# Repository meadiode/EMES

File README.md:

# EMES - Epic Minimalist Entertainment System

**EMES** - is a very minimalistic DIY handheld game console. 

Work in progress.

EMES has the following specifications:

 - Screen: 15x10 pixels, LED
 - Input: four button keyboard
 - Sound: Magnetic buzzer
 - Physical dimensions(approx): 40x32x14mm 
 - Removeable 8-pin cartridges

The console doesn't have an onboard CPU/MCU, instead an MCU is placed on every removable cartridge.

Each cartridge features an ATTiny10 MCU with the following specs:

 - Speed 8MHz
 - Peogram/data flash: 1KB
 - RAM: 32 bytes
 - IO: 4
 - ADC: 8bit

## Games

 - Pong
 - Snek - a snake variant, edge wrapping
 - Egg -  a N1ntend0 Game & Watch-like egg-catching game 
 - Brik - a Tetris-like
 - Simon - Simon Says

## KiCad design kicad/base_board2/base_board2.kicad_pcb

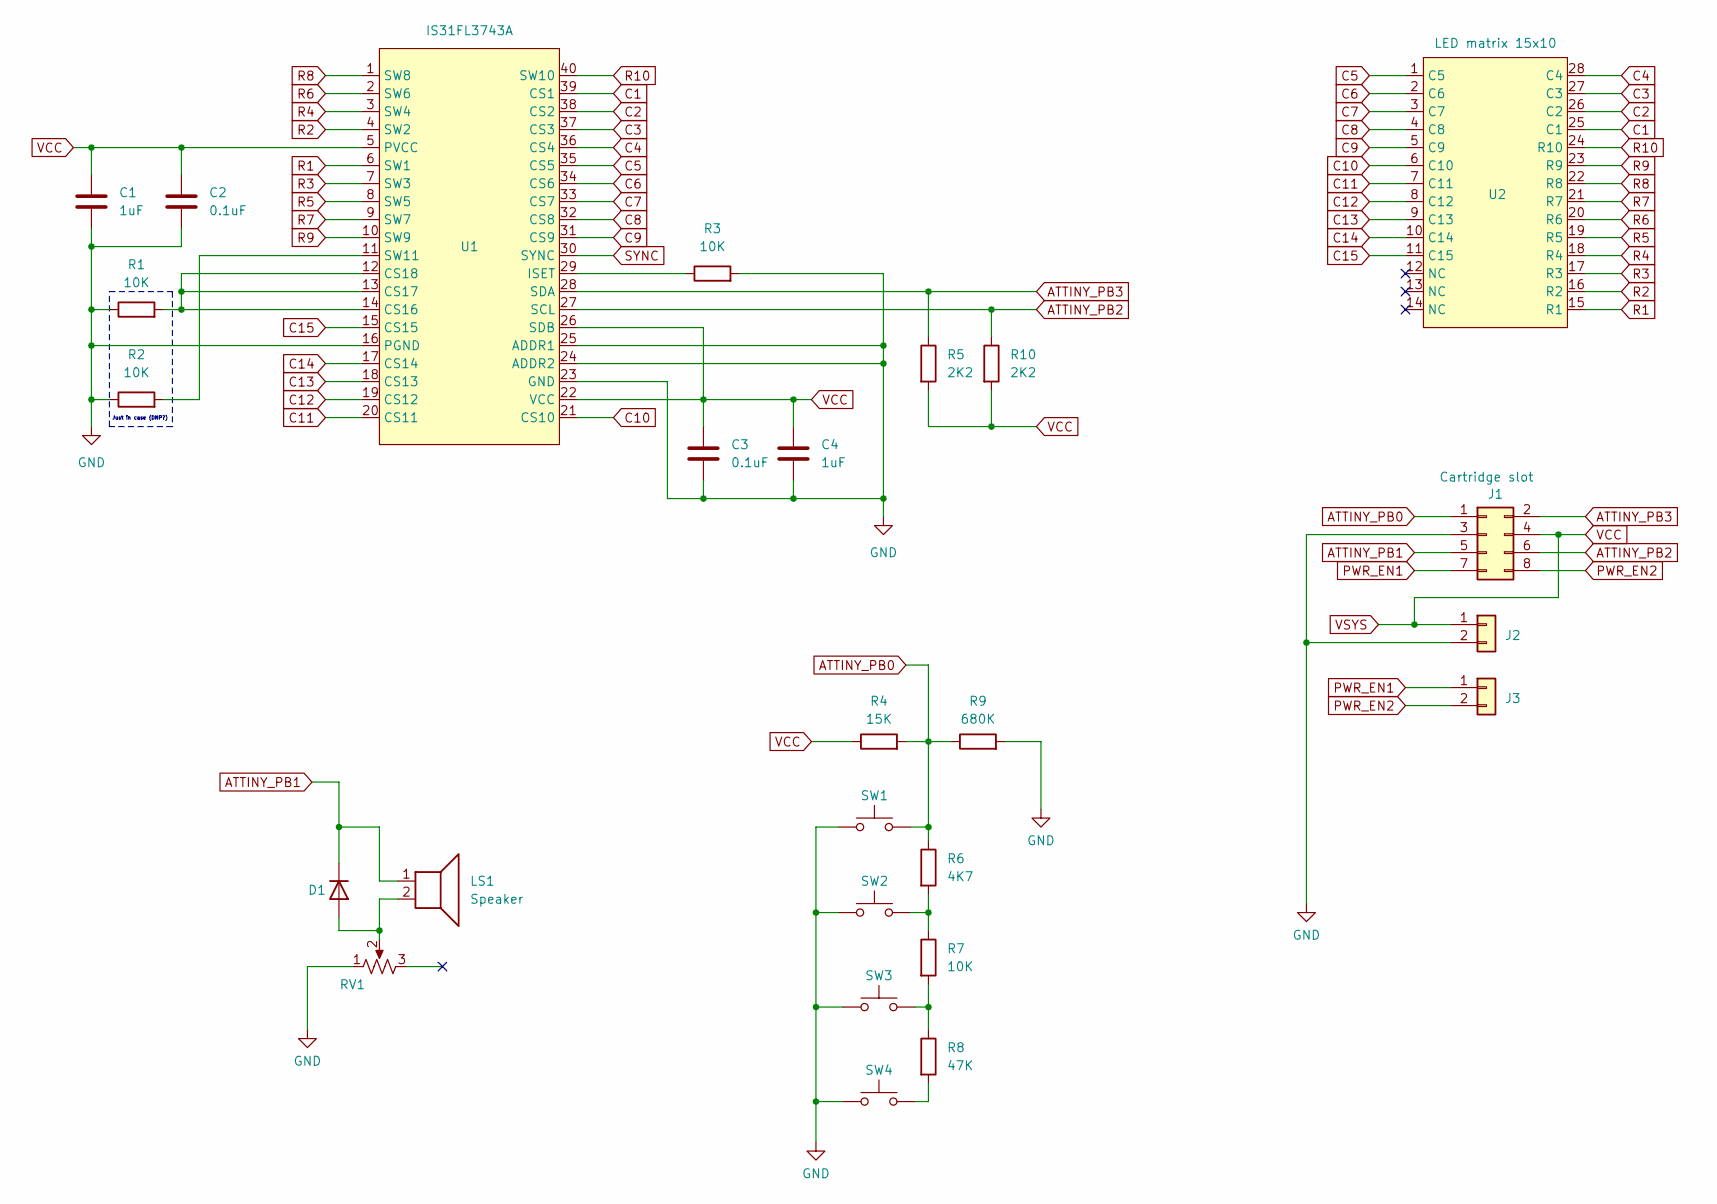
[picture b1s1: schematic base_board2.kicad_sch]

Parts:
C1, C4: 1uF; C_0603_1608Metric
C2, C3: 0.1uF; C_0603_1608Metric
D1: D; D_SOD-123
J1: Conn_02x04_Odd_Even; card_edge_2x4
J2, J3: Conn_01x02; Pads_1x2mm_2x
LS1: Speaker; Speaker_28908A
R1, R2, R3, R7: 10K; R_0603_1608Metric
R4: 15K; R_0603_1608Metric
R5, R10: 2K2; R_0603_1608Metric
R6: 4K7; R_0603_1608Metric
R8: 47K; R_0603_1608Metric
R9: 680K; R_0603_1608Metric
RV1: R_Potentiometer_US; ST-4EA
SW1, SW2, SW3, SW4: SW_Push; TS18_TACTILE_SWITCH
U1: IS31FL3743A; UQFN-40
U2: LED matrix 15x10; led_matrix_pcb_pads

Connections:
ATTINY_PB0: J1.1, R4.2, R6.1, R9.1, SW1.2
ATTINY_PB1: D1.1 (K), J1.5, LS1.1
ATTINY_PB2: J1.6, R10.1, U1.27 (SCL)
ATTINY_PB3: J1.2, R5.1, U1.28 (SDA)
C1: U1.39 (CS1), U2.25 (C1)
C2: U1.38 (CS2), U2.26 (C2)
C3: U1.37 (CS3), U2.27 (C3)
C4: U1.36 (CS4), U2.28 (C4)
C5: U1.35 (CS5), U2.1 (C5)
C6: U1.34 (CS6), U2.2 (C6)
C7: U1.33 (CS7), U2.3 (C7)
C8: U1.32 (CS8), U2.4 (C8)
C9: U1.31 (CS9), U2.5 (C9)
C10: U1.21 (CS10), U2.6 (C10)
C11: U1.20 (CS11), U2.7 (C11)
C12: U1.19 (CS12), U2.8 (C12)
C13: U1.18 (CS13), U2.9 (C13)
C14: U1.17 (CS14), U2.10 (C14)
C15: U1.15 (CS15), U2.11 (C15)
GND: C1.2, C2.2, C3.2, C4.2, J1.3, J2.2, R1.1, R2.1, R3.2, R9.2, RV1.1, SW1.1, SW2.1, SW3.1, SW4.1, U1.16 (PGND), U1.23 (GND), U1.24 (ADDR2), U1.25 (ADDR1)
unnamed: D1.2 (A), LS1.2, RV1.2
unnamed: R6.2, R7.1, SW2.2
unnamed: R7.2, R8.1, SW3.2
unnamed: R8.2, SW4.2
unnamed: R1.2, U1.12 (CS18), U1.13 (CS17), U1.14 (CS16)
unnamed: R3.1, U1.29 (ISET)
unnamed: R2.2, U1.11 (SW11)
PWR_EN1: J1.7, J3.1
PWR_EN2: J1.8, J3.2
R1: U1.6 (SW1), U2.15 (R1)
R2: U1.4 (SW2), U2.16 (R2)
R3: U1.7 (SW3), U2.17 (R3)
R4: U1.3 (SW4), U2.18 (R4)
R5: U1.8 (SW5), U2.19 (R5)
R6: U1.2 (SW6), U2.20 (R6)
R7: U1.9 (SW7), U2.21 (R7)
R8: U1.1 (SW8), U2.22 (R8)
R9: U1.10 (SW9), U2.23 (R9)
R10: U1.40 (SW10), U2.24 (R10)
SYNC: U1.30 (SYNC)
VCC: C1.1, C2.1, C3.1, C4.1, J1.4, J2.1, R4.1, R5.2, R10.2, U1.5 (PVCC), U1.22 (VCC), U1.26 (SDB)

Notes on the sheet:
Just in case (DNP?)

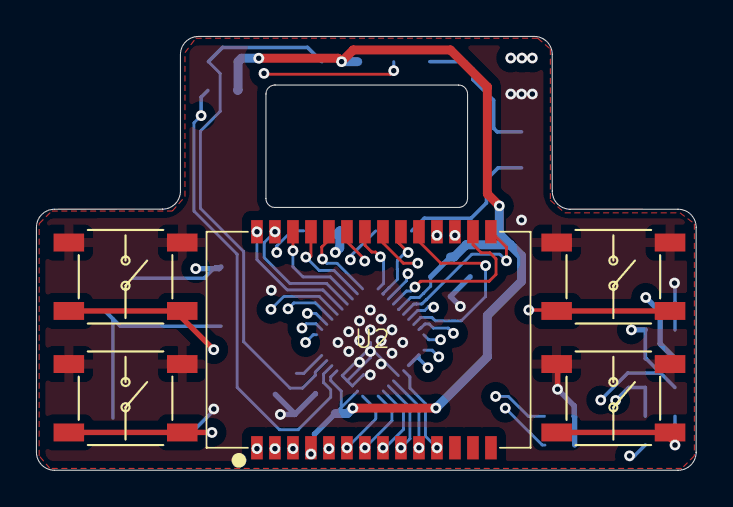
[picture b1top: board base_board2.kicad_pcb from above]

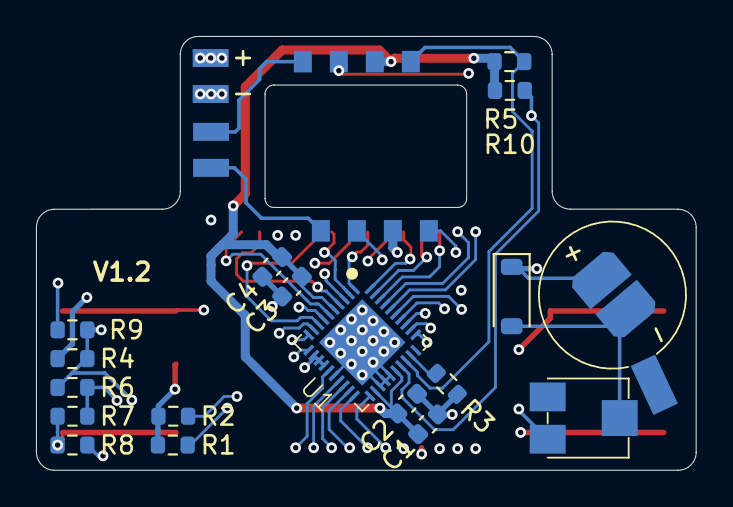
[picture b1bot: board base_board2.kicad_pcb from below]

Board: 4 copper layers, 36.7 x 24.1 mm, 26 parts (21 on the bottom side), 40 nets.

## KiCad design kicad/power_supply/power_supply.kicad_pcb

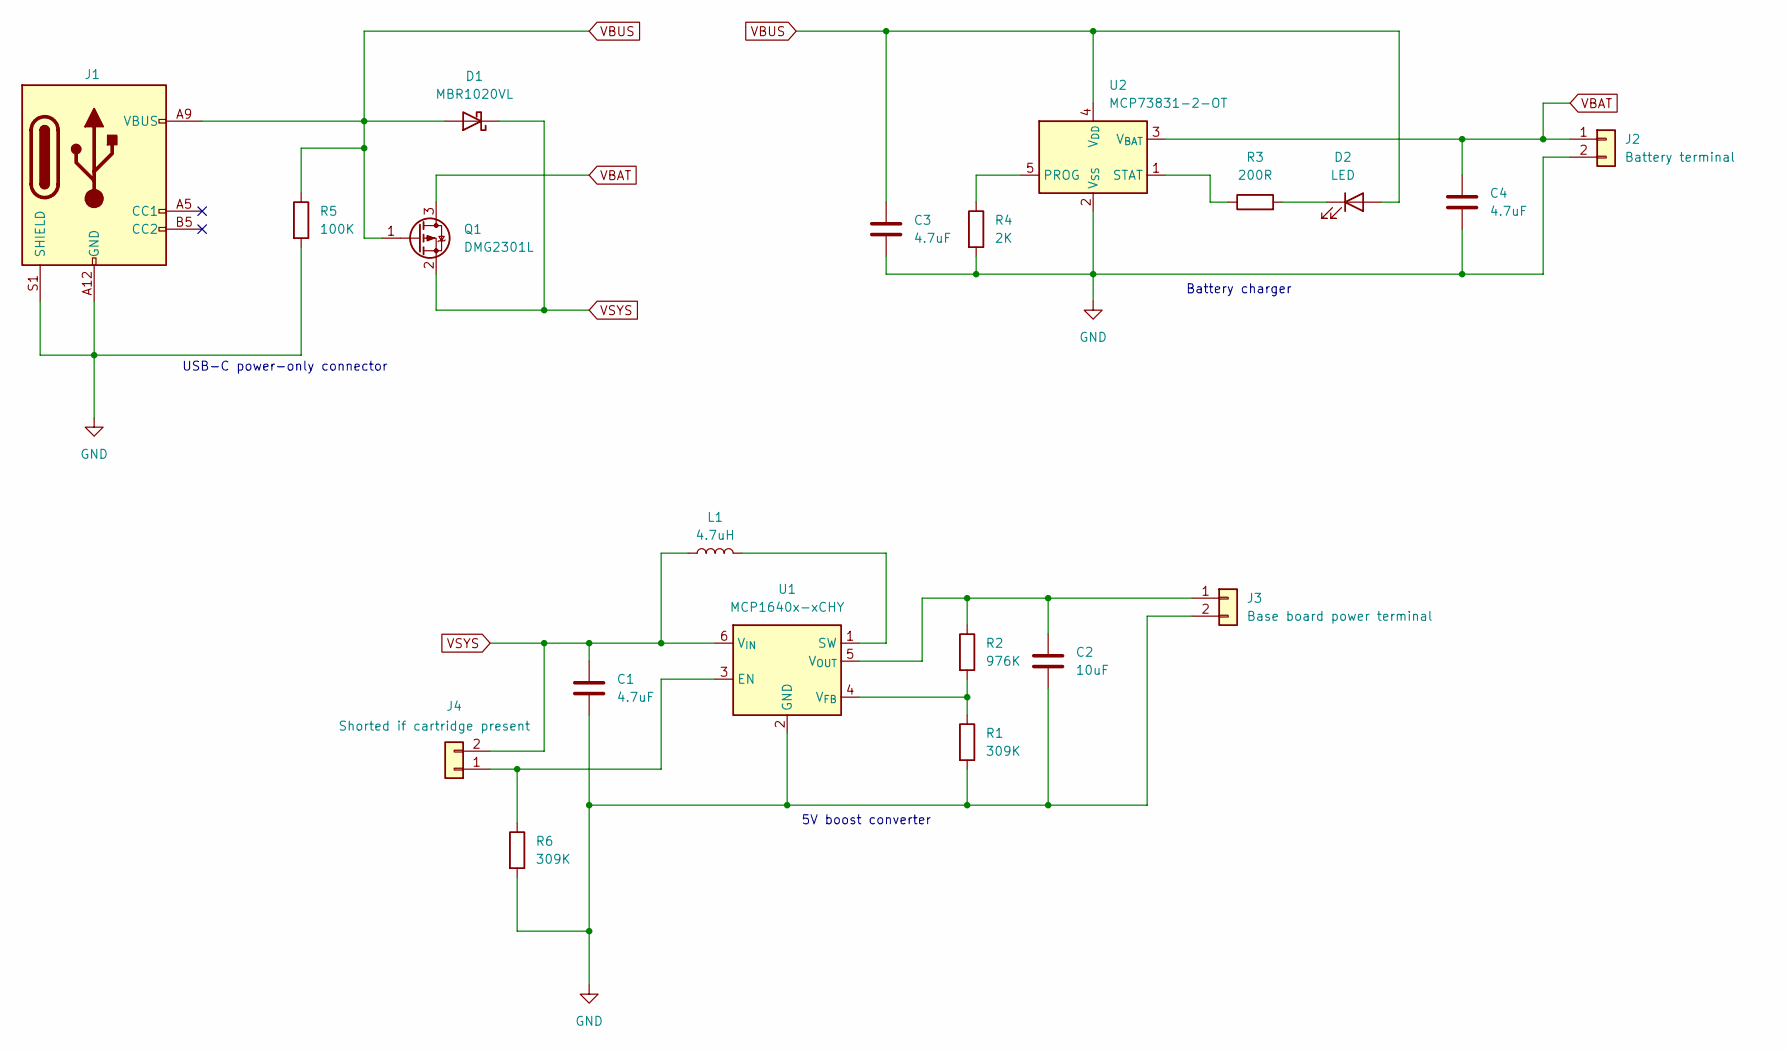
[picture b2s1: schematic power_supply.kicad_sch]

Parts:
C1, C3, C4: 4.7uF; C_0603_1608Metric
C2: 10uF; C_0603_1608Metric
D1: MBR1020VL; D_SOD-123F
D2: LED; LED_0603_1608Metric
J1: USB_C_Receptacle_PowerOnly_6P; USB_C_Receptacle_GCT_USB4125-xx-x_6P_TopMnt_Horizontal
J2: Battery terminal; Pads_1x2mm_2x
J3: Base board power terminal; Pads_1x2mm_2x
J4: Shorted if cartridge present; Pads_1x2mm_2x
L1: 4.7uH; L_Coilcraft_XAL5050-XXX
Q1: DMG2301L; SOT-23
R1, R6: 309K; R_0603_1608Metric
R2: 976K; R_0603_1608Metric
R3: 200R; R_0603_1608Metric
R4: 2K; R_0603_1608Metric
R5: 100K; R_0603_1608Metric
U1: MCP1640x-xCHY; SOT-23-6
U2: MCP73831-2-OT; SOT-23-5

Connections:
GND: C1.2, C2.2, C3.2, C4.2, J1.A12 (GND), J1.B12 (GND), J1.S1 (SHIELD), J2.2, J3.2, R1.2, R4.2, R5.2, R6.2, U1.2 (GND), U2.2 (V_{SS})
unnamed: D2.1 (K), R3.2
unnamed: C2.1, J3.1, R2.1, U1.5 (V_{OUT})
unnamed: J4.1, R6.1, U1.3 (EN)
unnamed: L1.2, U1.1 (SW)
unnamed: R1.1, R2.2, U1.4 (V_{FB})
unnamed: R4.1, U2.5 (PROG)
unnamed: R3.1, U2.1 (STAT)
VBAT: C4.1, J2.1, Q1.3 (D), U2.3 (V_{BAT})
VBUS: C3.1, D1.2 (A), D2.2 (A), J1.A9 (VBUS), J1.B9 (VBUS), Q1.1 (G), R5.1, U2.4 (V_{DD})
VSYS: C1.1, D1.1 (K), J4.2, L1.1, Q1.2 (S), U1.6 (V_{IN})

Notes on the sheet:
USB-C power-only connector
Battery charger
5V boost converter

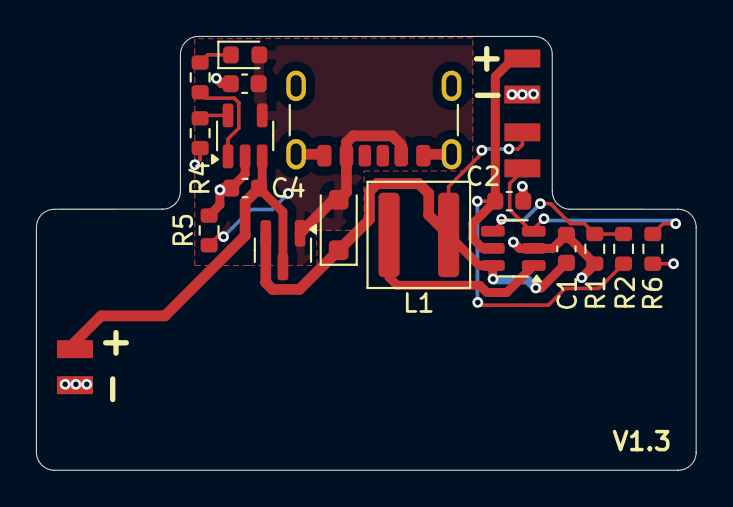
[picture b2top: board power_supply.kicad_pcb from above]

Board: 2 copper layers, 36.6 x 24.1 mm, 20 parts (0 on the bottom side), 11 nets.

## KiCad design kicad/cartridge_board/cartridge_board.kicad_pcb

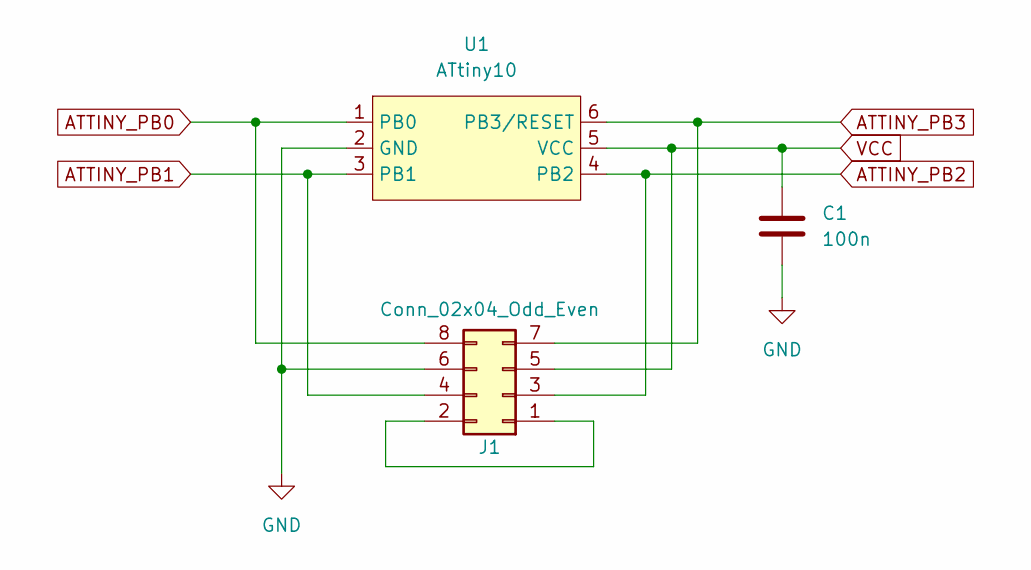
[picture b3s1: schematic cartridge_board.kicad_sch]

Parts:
C1: 100n; C_0603_1608Metric
J1: Conn_02x04_Odd_Even; board_edge_2x4
U1: ATtiny10; SOT-23-6

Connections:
ATTINY_PB0: J1.8, U1.1 (PB0)
ATTINY_PB1: J1.4, U1.3 (PB1)
ATTINY_PB2: J1.3, U1.4 (PB2)
ATTINY_PB3: J1.7, U1.6 (PB3/RESET)
GND: C1.2, J1.6, U1.2 (GND)
unnamed: J1.1, J1.2
VCC: C1.1, J1.5, U1.5 (VCC)

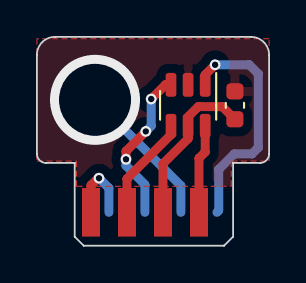
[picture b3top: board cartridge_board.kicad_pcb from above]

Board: 4 copper layers, 12.9 x 11.6 mm, 3 parts (0 on the bottom side), 7 nets.

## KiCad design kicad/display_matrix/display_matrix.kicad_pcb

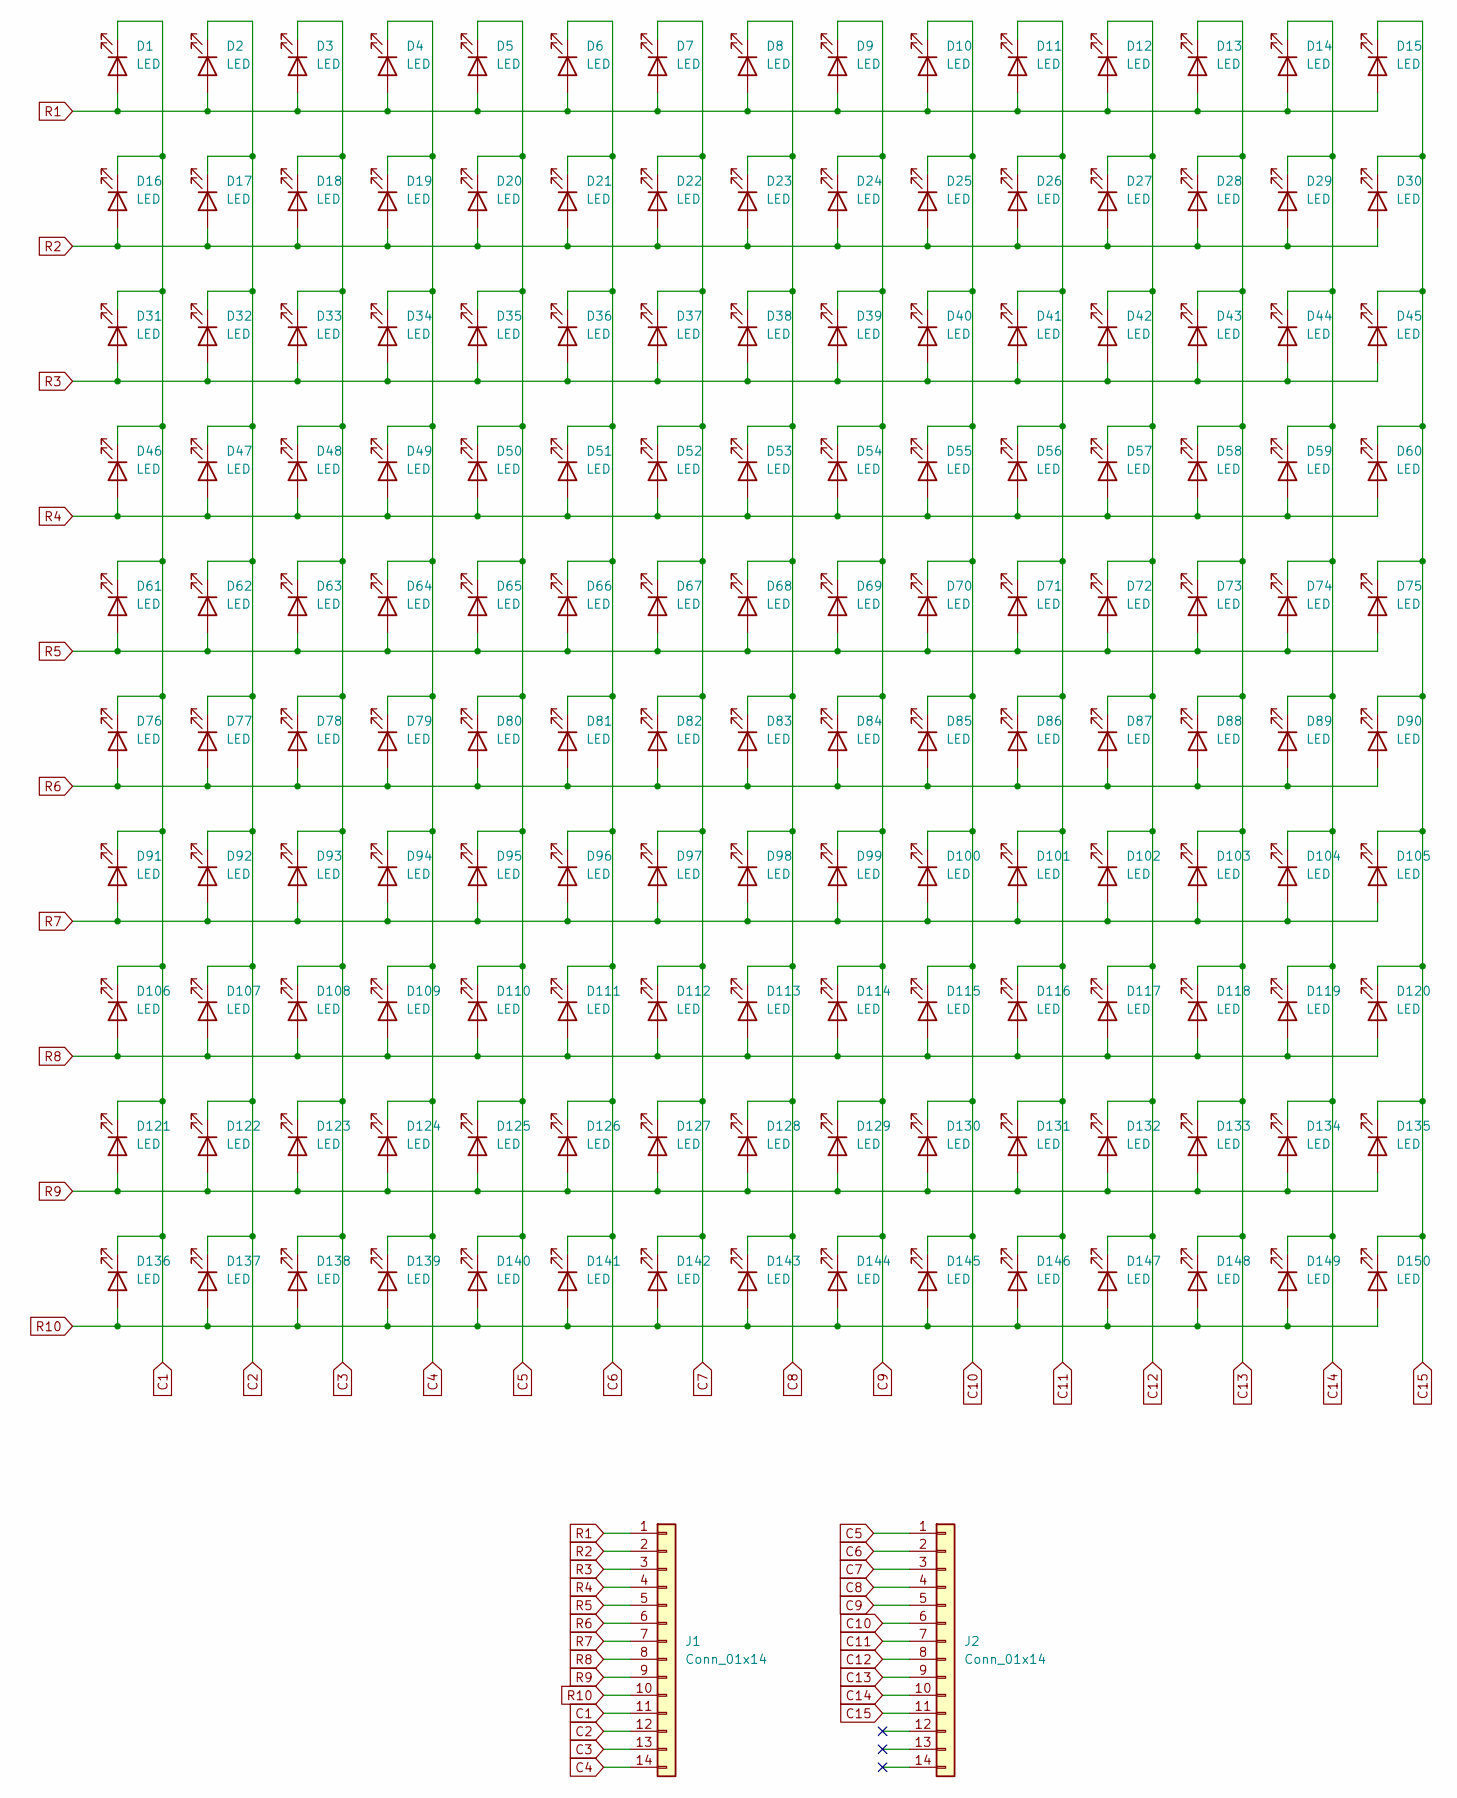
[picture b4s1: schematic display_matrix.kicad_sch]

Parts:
D1, D2, D3, D4, D5, D6, D7, D8, D9, D10, D11, D12, D13, D14, D15, D16, D17, D18, D19, D20, D21, D22, D23, D24, D25, D26, D27, D28, D29, D30, D31, D32, D33, D34, D35, D36, D37, D38, D39, D40, D41, D42, D43, D44, D45, D46, D47, D48, D49, D50, D51, D52, D53, D54, D55, D56, D57, D58, D59, D60, D61, D62, D63, D64, D65, D66, D67, D68, D69, D70, D71, D72, D73, D74, D75, D76, D77, D78, D79, D80, D81, D82, D83, D84, D85, D86, D87, D88, D89, D90, D91, D92, D93, D94, D95, D96, D97, D98, D99, D100, D101, D102, D103, D104, D105, D106, D107, D108, D109, D110, D111, D112, D113, D114, D115, D116, D117, D118, D119, D120, D121, D122, D123, D124, D125, D126, D127, D128, D129, D130, D131, D132, D133, D134, D135, D136, D137, D138, D139, D140, D141, D142, D143, D144, D145, D146, D147, D148, D149, D150: LED; LED_XL-0201UYC
J1, J2: Conn_01x14; Castellated_edge_14_1mm

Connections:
C1: D1.1 (K), D16.1 (K), D31.1 (K), D46.1 (K), D61.1 (K), D76.1 (K), D91.1 (K), D106.1 (K), D121.1 (K), D136.1 (K), J1.11
C2: D2.1 (K), D17.1 (K), D32.1 (K), D47.1 (K), D62.1 (K), D77.1 (K), D92.1 (K), D107.1 (K), D122.1 (K), D137.1 (K), J1.12
C3: D3.1 (K), D18.1 (K), D33.1 (K), D48.1 (K), D63.1 (K), D78.1 (K), D93.1 (K), D108.1 (K), D123.1 (K), D138.1 (K), J1.13
C4: D4.1 (K), D19.1 (K), D34.1 (K), D49.1 (K), D64.1 (K), D79.1 (K), D94.1 (K), D109.1 (K), D124.1 (K), D139.1 (K), J1.14
C5: D5.1 (K), D20.1 (K), D35.1 (K), D50.1 (K), D65.1 (K), D80.1 (K), D95.1 (K), D110.1 (K), D125.1 (K), D140.1 (K), J2.1
C6: D6.1 (K), D21.1 (K), D36.1 (K), D51.1 (K), D66.1 (K), D81.1 (K), D96.1 (K), D111.1 (K), D126.1 (K), D141.1 (K), J2.2
C7: D7.1 (K), D22.1 (K), D37.1 (K), D52.1 (K), D67.1 (K), D82.1 (K), D97.1 (K), D112.1 (K), D127.1 (K), D142.1 (K), J2.3
C8: D8.1 (K), D23.1 (K), D38.1 (K), D53.1 (K), D68.1 (K), D83.1 (K), D98.1 (K), D113.1 (K), D128.1 (K), D143.1 (K), J2.4
C9: D9.1 (K), D24.1 (K), D39.1 (K), D54.1 (K), D69.1 (K), D84.1 (K), D99.1 (K), D114.1 (K), D129.1 (K), D144.1 (K), J2.5
C10: D10.1 (K), D25.1 (K), D40.1 (K), D55.1 (K), D70.1 (K), D85.1 (K), D100.1 (K), D115.1 (K), D130.1 (K), D145.1 (K), J2.6
C11: D11.1 (K), D26.1 (K), D41.1 (K), D56.1 (K), D71.1 (K), D86.1 (K), D101.1 (K), D116.1 (K), D131.1 (K), D146.1 (K), J2.7
C12: D12.1 (K), D27.1 (K), D42.1 (K), D57.1 (K), D72.1 (K), D87.1 (K), D102.1 (K), D117.1 (K), D132.1 (K), D147.1 (K), J2.8
C13: D13.1 (K), D28.1 (K), D43.1 (K), D58.1 (K), D73.1 (K), D88.1 (K), D103.1 (K), D118.1 (K), D133.1 (K), D148.1 (K), J2.9
C14: D14.1 (K), D29.1 (K), D44.1 (K), D59.1 (K), D74.1 (K), D89.1 (K), D104.1 (K), D119.1 (K), D134.1 (K), D149.1 (K), J2.10
C15: D15.1 (K), D30.1 (K), D45.1 (K), D60.1 (K), D75.1 (K), D90.1 (K), D105.1 (K), D120.1 (K), D135.1 (K), D150.1 (K), J2.11
R1: D1.2 (A), D2.2 (A), D3.2 (A), D4.2 (A), D5.2 (A), D6.2 (A), D7.2 (A), D8.2 (A), D9.2 (A), D10.2 (A), D11.2 (A), D12.2 (A), D13.2 (A), D14.2 (A), D15.2 (A), J1.1
R2: D16.2 (A), D17.2 (A), D18.2 (A), D19.2 (A), D20.2 (A), D21.2 (A), D22.2 (A), D23.2 (A), D24.2 (A), D25.2 (A), D26.2 (A), D27.2 (A), D28.2 (A), D29.2 (A), D30.2 (A), J1.2
R3: D31.2 (A), D32.2 (A), D33.2 (A), D34.2 (A), D35.2 (A), D36.2 (A), D37.2 (A), D38.2 (A), D39.2 (A), D40.2 (A), D41.2 (A), D42.2 (A), D43.2 (A), D44.2 (A), D45.2 (A), J1.3
R4: D46.2 (A), D47.2 (A), D48.2 (A), D49.2 (A), D50.2 (A), D51.2 (A), D52.2 (A), D53.2 (A), D54.2 (A), D55.2 (A), D56.2 (A), D57.2 (A), D58.2 (A), D59.2 (A), D60.2 (A), J1.4
R5: D61.2 (A), D62.2 (A), D63.2 (A), D64.2 (A), D65.2 (A), D66.2 (A), D67.2 (A), D68.2 (A), D69.2 (A), D70.2 (A), D71.2 (A), D72.2 (A), D73.2 (A), D74.2 (A), D75.2 (A), J1.5
R6: D76.2 (A), D77.2 (A), D78.2 (A), D79.2 (A), D80.2 (A), D81.2 (A), D82.2 (A), D83.2 (A), D84.2 (A), D85.2 (A), D86.2 (A), D87.2 (A), D88.2 (A), D89.2 (A), D90.2 (A), J1.6
R7: D91.2 (A), D92.2 (A), D93.2 (A), D94.2 (A), D95.2 (A), D96.2 (A), D97.2 (A), D98.2 (A), D99.2 (A), D100.2 (A), D101.2 (A), D102.2 (A), D103.2 (A), D104.2 (A), D105.2 (A), J1.7
R8: D106.2 (A), D107.2 (A), D108.2 (A), D109.2 (A), D110.2 (A), D111.2 (A), D112.2 (A), D113.2 (A), D114.2 (A), D115.2 (A), D116.2 (A), D117.2 (A), D118.2 (A), D119.2 (A), D120.2 (A), J1.8
R9: D121.2 (A), D122.2 (A), D123.2 (A), D124.2 (A), D125.2 (A), D126.2 (A), D127.2 (A), D128.2 (A), D129.2 (A), D130.2 (A), D131.2 (A), D132.2 (A), D133.2 (A), D134.2 (A), D135.2 (A), J1.9
R10: D136.2 (A), D137.2 (A), D138.2 (A), D139.2 (A), D140.2 (A), D141.2 (A), D142.2 (A), D143.2 (A), D144.2 (A), D145.2 (A), D146.2 (A), D147.2 (A), D148.2 (A), D149.2 (A), D150.2 (A), J1.10

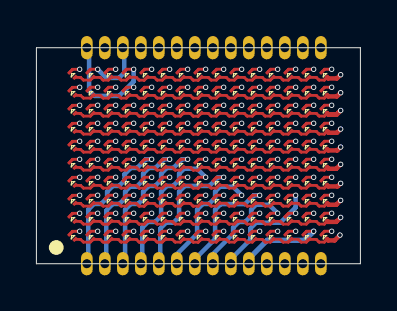
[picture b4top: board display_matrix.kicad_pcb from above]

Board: 4 copper layers, 18.0 x 12.0 mm, 152 parts (0 on the bottom side), 25 nets.

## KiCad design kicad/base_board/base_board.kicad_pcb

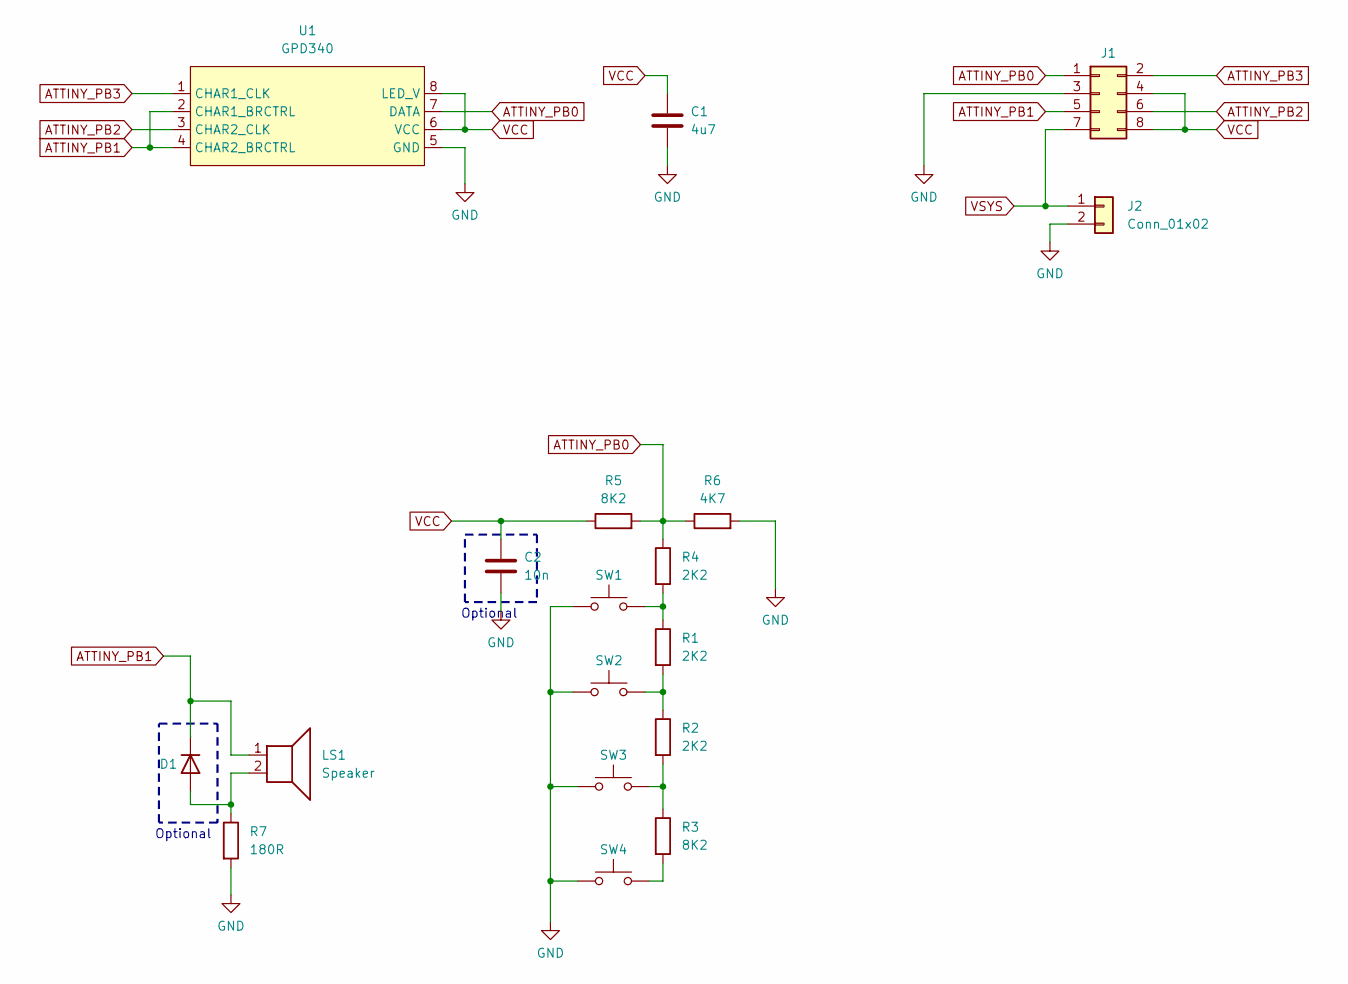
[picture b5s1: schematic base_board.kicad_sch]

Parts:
C1: 4u7; C_0603_1608Metric
C2: 10n; C_0603_1608Metric
D1: D; D_SOD-123
J1: Conn_02x04_Odd_Even; card_edge_2x4
J2: Conn_01x02; PinHeader_1x02_P2.54mm_Vertical
LS1: Speaker; BUZZER_CMT-0525
R1, R2, R4: 2K2; R_0603_1608Metric
R3, R5: 8K2; R_0603_1608Metric
R6: 4K7; R_0603_1608Metric
R7: 180R; R_0603_1608Metric
SW1, SW2, SW3, SW4: SW_Push; TS18_TACTILE_SWITCH
U1: GPD340; DIP-8_W7.62mm_Socket

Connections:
ATTINY_PB0: J1.1, R4.1, R5.2, R6.1, U1.7 (DATA)
ATTINY_PB1: D1.1 (K), J1.5, LS1.1, U1.2 (CHAR1_BRCTRL), U1.4 (CHAR2_BRCTRL)
ATTINY_PB2: J1.6, U1.3 (CHAR2_CLK)
ATTINY_PB3: J1.2, U1.1 (CHAR1_CLK)
GND: C1.2, C2.2, J1.3, J2.2, R6.2, R7.2, SW1.1, SW2.1, SW3.1, SW4.1, U1.5 (GND)
unnamed: D1.2 (A), LS1.2, R7.1
unnamed: R1.1, R4.2, SW1.2
unnamed: R1.2, R2.1, SW2.2
unnamed: R2.2, R3.1, SW3.2
unnamed: R3.2, SW4.2
VCC: C1.1, C2.1, J1.4, J1.8, R5.1, U1.6 (VCC), U1.8 (LED_V)
VSYS: J1.7, J2.1

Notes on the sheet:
Optional

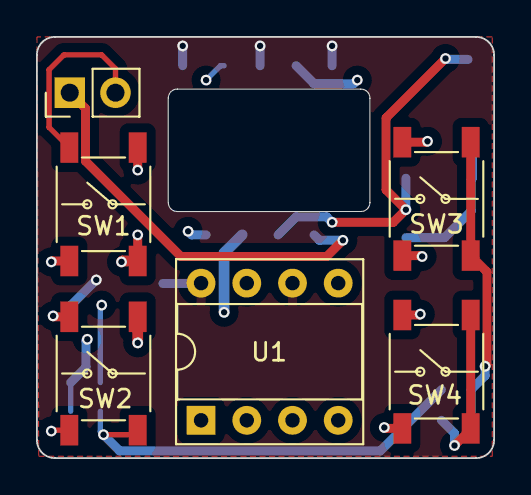
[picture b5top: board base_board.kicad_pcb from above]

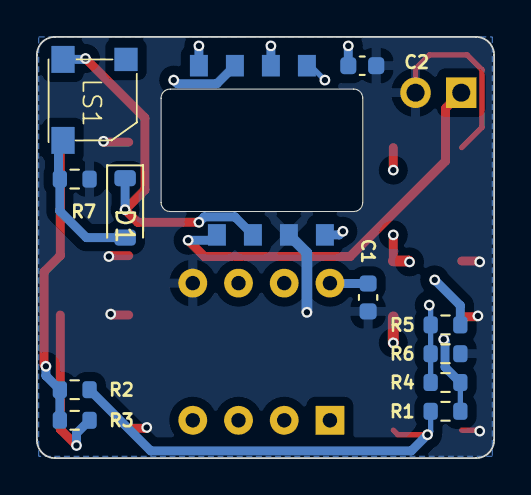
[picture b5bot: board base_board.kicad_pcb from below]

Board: 4 copper layers, 25.4 x 23.4 mm, 18 parts (12 on the bottom side), 12 nets.

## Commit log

2024-08-20 experiments with attiny10; add demo.c
2024-08-20 new makefile; add .gitignore
2024-08-21 add breadboard kicad/pdf schematics
2024-08-21 drive speaker directly
2024-08-24 add barely playable pong
2024-08-29 rewriting pong in assembly - almost there
2024-08-31 work on pong.S
2024-09-06 adjust keyboard ADC values; assembly pong: add score counter, paddle choice, start/end game
2024-09-06 add readme, images, and LOICENSE
2024-09-06 update readme; add pong jif
2024-09-07 work on snake.S
2024-09-08 snake.S - snake decoding/drawing procedure
2024-09-09 add kicad projects for baseboard and cartridge
2024-09-10 snake moves properly
2024-09-10 snake.S - spawning and eating food
2024-09-11 self-bite check/end game
2024-09-11 snake fully playable + show score
2024-09-12 add snek jif, update readme
2025-05-03 work on LED matrix & driver PCBs
2025-05-11 minor PCB fixes - display led matrix, standalone driver module
2025-05-24 playing with is31fl3743a/evaluation demo
2025-05-25 play bad apple; fix an oopsie in the driver schematics/pcb
2025-05-31 experiments with bitbanged i2c reading/writing
2025-06-01 new proto breadboard & initial demo for tiny10
2025-06-19 new test utility program; displaying monochormo images
2025-06-21 rewrite pong.S for the new display
2025-07-04 base_board-v2 & power_supply PCBs
2025-07-06 rewriting snek.S
2025-07-11 rewrite snek
2025-07-12 work on brik.S
2025-07-13 brik.S - pieces rotation, full rows collapse
2025-07-18 playable brik.S; resistor ladder change for wider voltage gap between keys
2025-07-20 work on egg.S
2025-07-26 fix an oopsie on base_board2
2025-07-26 almost playable egg
2025-08-02 initial version of housing & cartridge storage container; minor changes in the PCBs; improve egg.S
2025-08-03 3dcad/housing - smol adjustments & improvements
2025-08-17 3dcad/housing - better key chain hole with a snap joint
2026-02-14 pcbs: improve powering scheme, redesign cartridge; 3dcad: update whole housing
2026-02-15 3dcad/housing: top part blind version
2026-03-21 add smol game logos
2026-03-22 flip cartridge pcb
2026-03-22 cartridge pcb panelized; smol fixes to baseboard pcb
2026-03-28 3dcad/housing - refactor; options for heatserts & blind top
2026-04-25 3dcad/housing: fdm & sla variants; kicad/power_supply: add p-down resistor to the MCP1640's EN pin
2026-04-25 pong/snek/brik/test_util.S: small updates; brik.S: add speedup logic, game over tune
2026-04-26 simon.S - gameplay, intro & display score
2026-04-26 update README & cad pictures
2026-05-02 playable stak.S
2026-05-03 stak.S - show final score & restart game
2026-05-10 initial work on birb.S - moving pipes
